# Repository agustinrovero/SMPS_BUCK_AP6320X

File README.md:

# Mini 2A Buck Converter SMPS (AP6320X Family)

This repository contains the hardware design files in **KiCad** for an ultra-compact, high-efficiency **2A synchronous buck (step-down) converter**. The board layout is fully compatible with all four variants of the **AP6320X** integrated circuit from Diodes Incorporated, allowing the same PCB to be populated for different switching frequencies, operating modes, and output voltages.

## Technical Specifications

* **Input Voltage Range ($V_{IN}$):** 3.8 V to 32 V
* **Continuous Output Current ($I_{OUT}$):** 2 A
* **EMI Optimization:** Features Frequency Spread Spectrum (FSS) and a proprietary gate driver system to eliminate switching node ringing without external components.
* **Form Factor:** $14.4\times15.4\text{ mm}^2$ mini-size PCB layout optimized for tight spaces and minimal current loops.

---

## IC Variant Compatibility Matrix

The base PCB accommodates any of the four chip versions. Your component selection for the feedback network ($R_1$ and $R_2$) depends entirely on the specific IC you choose to solder:

| Variant | Frequency | Light-Load Mode | Output Voltage | PCB Assembly Note |
| :--- | :--- | :--- | :--- | :--- |
| **AP63200** | 500 kHz | PFM (High Efficiency) | Adjustable (0.8 V to $V_{IN}$) | Populate feedback resistors $R_1$ and $R_2$, and capacitor $C_{f1}$ |
| **AP63201** | 500 kHz | Forced PWM | Adjustable (0.8 V to $V_{IN}$) | Populate feedback resistors $R_1$ and $R_2$, and capacitor $C_{f1}$ |
| **AP63203** | 1.1 MHz | PFM (High Efficiency) | **Fixed 3.3 V** | Solder $0\,\Omega$ jumper on $R_1$, omit $R_2$ |
| **AP63205** | 1.1 MHz | PFM (High Efficiency) | **Fixa 5.0 V** | Solder $0\,\Omega$ jumper on $R_1$, omit $R_2$ |

---

## Repository Structure

* `Hardware`: Core KiCad project files (`.kicad_pro`, `.kicad_sch`, `.kicad_pcb`).
* `Docs`: Component [datasheets](https://diodes.com) and reference application notes.
* `Outputs/3D`:
* `Outputs/BOM`: Interactive Bill of Materials (iBOM) and CSV component list.
* `Outputs/Gerbers`: Production-ready Gerber and NC Drill files.

---

## Component Specifications & Form Factor

* **Passives:** All capacitors, resistors, and LEDs utilize compact **0603** SMD packages to minimize the board footprint.
* **Power Inductor ($L_1$):** Designed with a standard **$6\times 6\text{ mm}$** footprint.
  * The default inductor handles the full 2 A output requirement.
  * For lower profile or lower current applications, alternative inductors like the **Abracon ASPI-0628-6R8M-T1** can be used (supports up to 1.5 A with a height of only 2.8 mm instead of 4.5 mm).

---

## Critical Component Selection

* **Power Inductor ($L_1$):** Shielded power inductor with a saturation current ($I_{SAT}$) rating strictly above **3 A** to prevent saturation during load transients.
* **Input/Output Capacitors ($C_{IN}$ / $C_{OUT}$):** **X7R** or **X5R** MLCC ceramic capacitors for low ESR and high capacitance retention under DC bias.
* **Feedback Resistors:** **1% tolerance** SMD resistors to maintain excellent target voltage accuracy (for adjustable versions).

---

## Requirements

* Designed and verified using **KiCad v9.0.8**.

## License

This open-source hardware project is distributed under the **CERN OHL-W v2** (CERN Open Hardware Licence Weak) or equivalent open-source standard.

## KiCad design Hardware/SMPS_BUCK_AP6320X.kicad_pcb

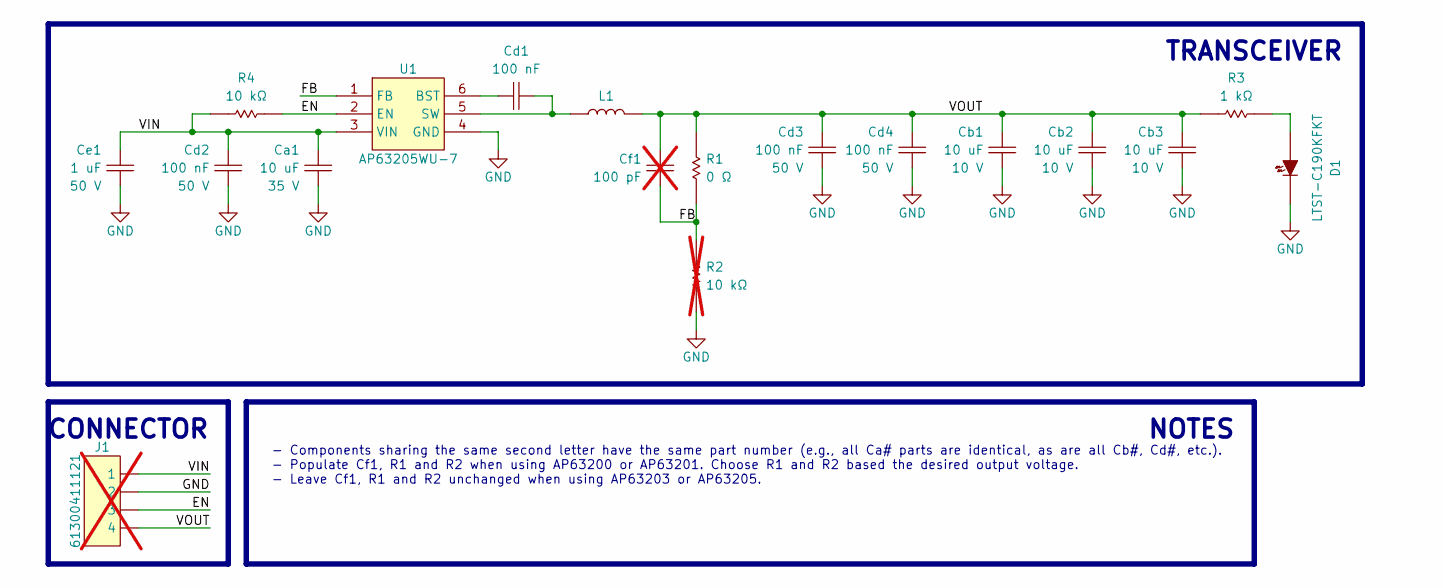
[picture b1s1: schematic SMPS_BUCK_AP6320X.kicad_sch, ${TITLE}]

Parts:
Ca1: 10 uF; Samsung_Electro-Mechanics_CL10B104JB8NNNC; Tolerance 20 %; Voltage 35 V; MPN GRM188R6YA106MA73D
Cb1, Cb2, Cb3: 10 uF; Samsung_Electro-Mechanics_CL10B104JB8NNNC; Tolerance 10 %; Voltage 10 V; MPN GRM188Z71A106KA73D
Cd1, Cd2, Cd3, Cd4: 100 nF; Samsung_Electro-Mechanics_CL10B104JB8NNNC; Tolerance 5 %; Voltage 50 V; MPN CL10B104JB8NNNC
Ce1: 1 uF; Samsung_Electro-Mechanics_CL10B104JB8NNNC; Tolerance 10 %; Voltage 50 V; MPN CL10A105KB8NNNC
Cf1: 100 pF; Samsung_Electro-Mechanics_CL10B104JB8NNNC; Tolerance 5 %; Voltage 50 V; MPN CL10C101JB8NNNC; not fitted
D1: LTST-C190KFKT; Lite-On_LTST-C190KFKT; MPN LTST-C190KFKT
J1: 61300411121; Würth_Elektronik_61300411121; MPN 61300411121; not fitted
L1: Abracon LLC ASPI-6045S-6R8M-T; Abracon_LLC_ASPI-6045S-6R8M-T; MPN ASPI-6045S-6R8M-T
R1: 0 Ω; YAGEO_RC0603FR-070RL; Tolerance 1 %; MPN RC0603FR-070RL
R2: 10 kΩ; YAGEO_RC0603FR-070RL; Tolerance 1 %; MPN RC0603FR-0710KL; not fitted
R3: 1 kΩ; YAGEO_RC0603FR-070RL; Tolerance 1 %; MPN RC0603FR-071KL
R4: 10 kΩ; YAGEO_RC0603FR-070RL; Tolerance 1 %; MPN RC0603FR-0710KL
U1: AP63205WU-7; TSOT23-6; MPN AP63205WU-7

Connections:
/EN: J1.3, R4.1, U1.2 (EN)
/FB: Cf1.1, R1.1, R2.2, U1.1 (FB)
/VIN: Ca1.2, Cd2.2, Ce1.2, J1.1, R4.2, U1.3 (VIN)
/VOUT: Cb1.2, Cb2.2, Cb3.2, Cd3.2, Cd4.2, Cf1.2, J1.4, L1.2, R1.2, R3.1
GND: Ca1.1, Cb1.1, Cb2.1, Cb3.1, Cd2.1, Cd3.1, Cd4.1, Ce1.1, D1.K, J1.2, R2.1, U1.4 (GND)
unnamed: D1.A, R3.2
unnamed: Cd1.1, U1.6 (BST)
unnamed: Cd1.2, L1.1, U1.5 (SW)

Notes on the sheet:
CONNECTOR
TRANSCEIVER
NOTES
- Components sharing the same second letter have the same part number (e.g., all Ca# parts are identical, as are all Cb#, Cd#, etc.). - Populate Cf1, R1 and R2 when using AP63200 or AP63201. Choose R1 and R2 based the desired output voltage. - Leave Cf1, R1 and R2 unchanged when using AP63203 or AP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

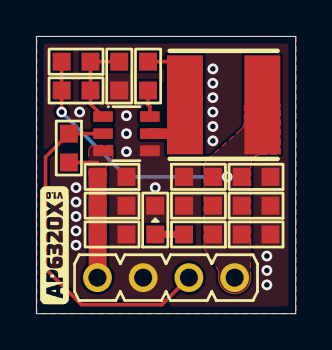
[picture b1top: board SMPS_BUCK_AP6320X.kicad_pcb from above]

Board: 2 copper layers, 14.4 x 15.4 mm, 18 parts (1 on the bottom side), 8 nets.

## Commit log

2026-06-24 New layout.
2026-06-24 Removed backup files.
2026-06-24 Added git ignore.
2026-06-24 Updated git ignore.
2026-06-25 Changed inductor and layout.
2026-06-25 Added README file and PCB logos.
2026-06-25 Files are now placed into folders.
2026-06-26 Added BOM files, 3D and unit prices to BOM.
2026-06-26 Added shcematic file.
2026-06-26 cHANGES TO readme.
